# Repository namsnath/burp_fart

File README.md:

# burp_fart
A 3x5+3 split, diode-less keyboard with support for a rotary encoder.

## PCB

## Schematic

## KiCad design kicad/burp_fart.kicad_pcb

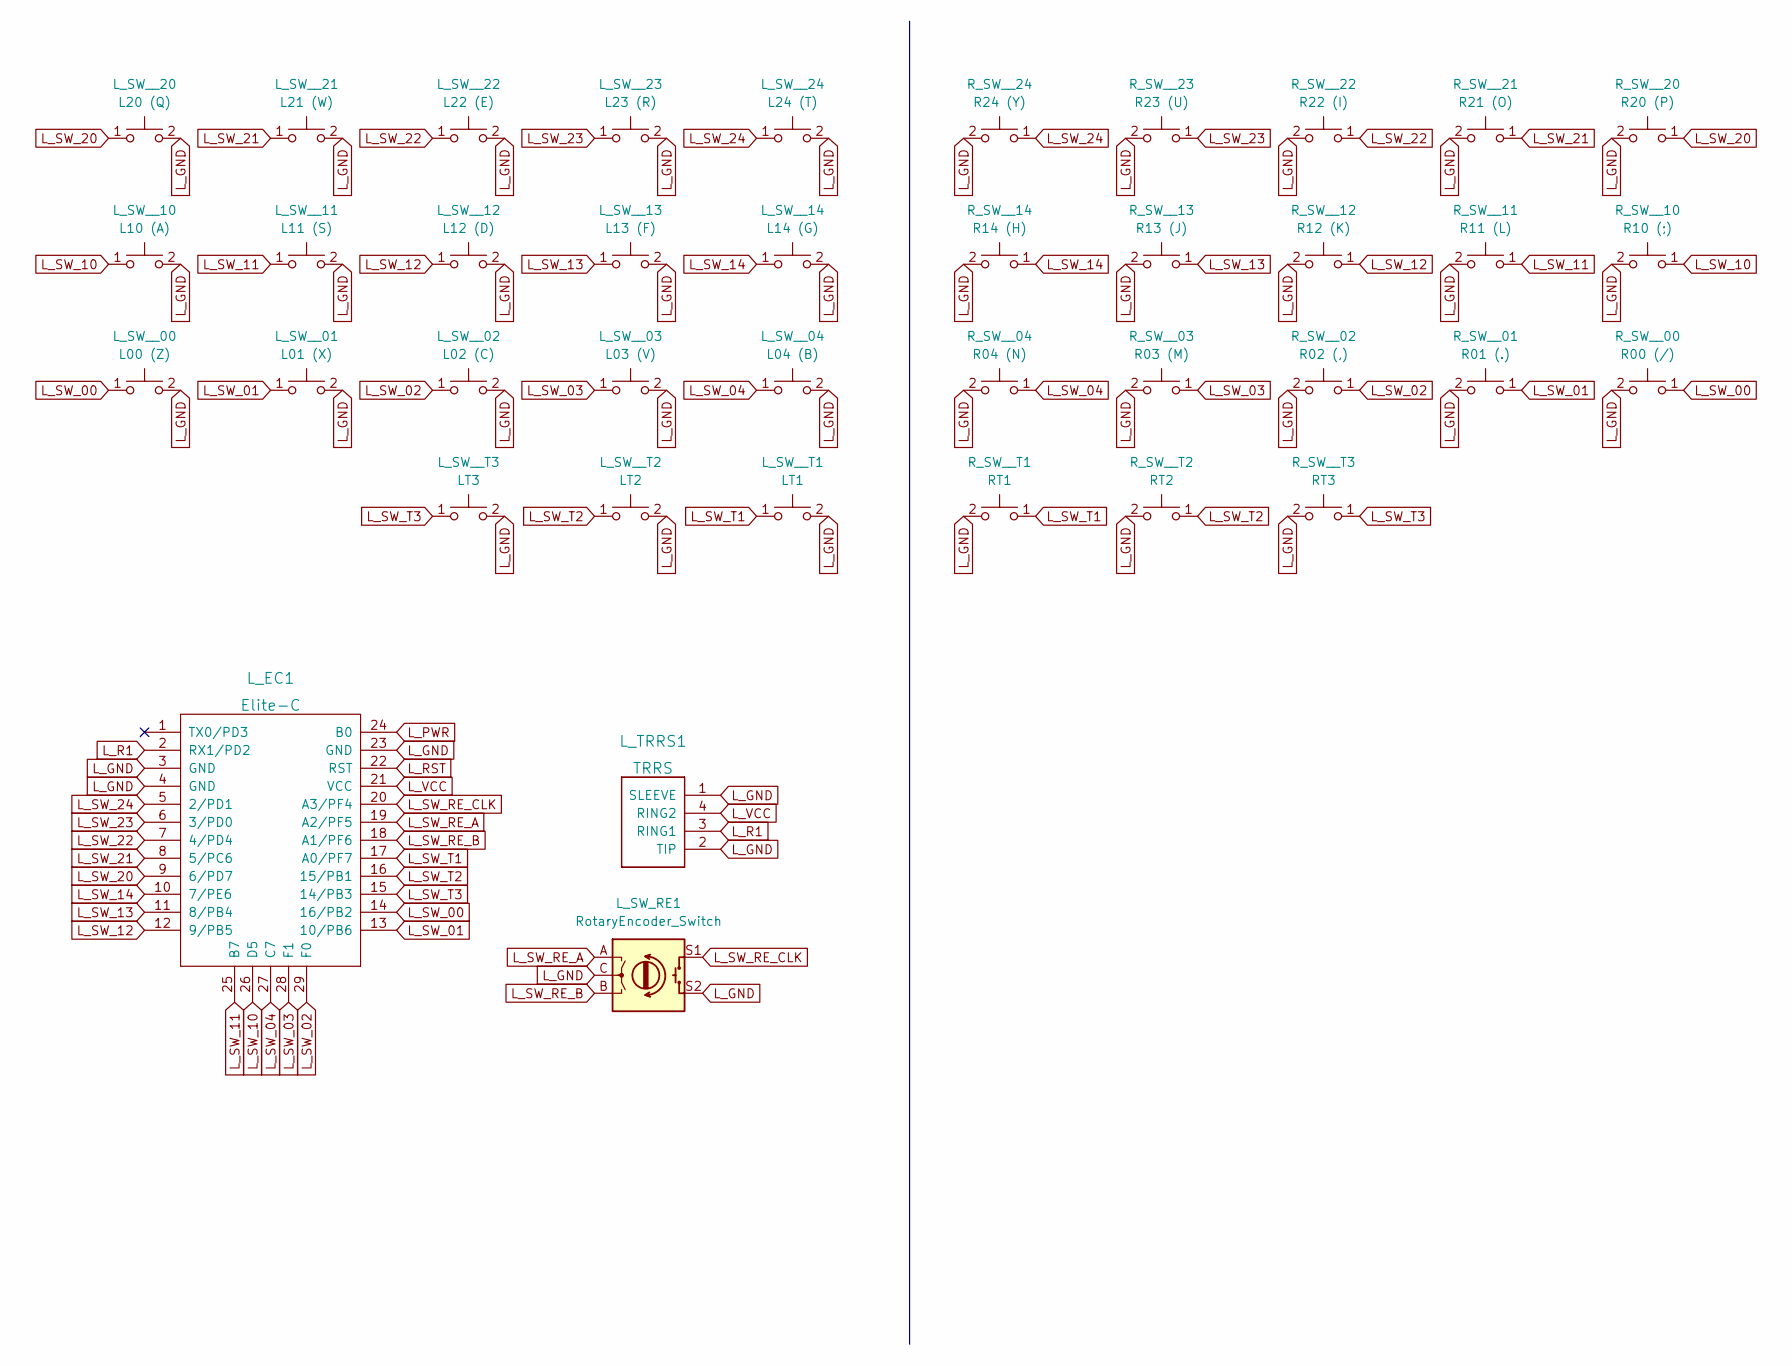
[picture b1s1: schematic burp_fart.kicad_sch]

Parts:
L_EC1: Elite-C
L_SW_RE1: RotaryEncoder_Switch; RotaryEncoder_Alps_EC11E-Switch_Vertical_H20mm
L_SW__00: L00 (Z); Kailh_socket_MX_pads_flipped
L_SW__01: L01 (X); Kailh_socket_MX_pads_flipped
L_SW__02: L02 (C); Kailh_socket_MX_pads_flipped
L_SW__03: L03 (V); Kailh_socket_MX_pads_flipped
L_SW__04: L04 (B); Kailh_socket_MX_pads_flipped
L_SW__10: L10 (A); Kailh_socket_MX_pads_flipped
L_SW__11: L11 (S); Kailh_socket_MX_pads_flipped
L_SW__12: L12 (D); Kailh_socket_MX_pads_flipped
L_SW__13: L13 (F); Kailh_socket_MX_pads_flipped
L_SW__14: L14 (G); Kailh_socket_MX_pads_flipped
L_SW__20: L20 (Q); Kailh_socket_MX_pads_flipped
L_SW__21: L21 (W); Kailh_socket_MX_pads_flipped
L_SW__22: L22 (E); Kailh_socket_MX_pads_flipped
L_SW__23: L23 (R); Kailh_socket_MX_pads_flipped
L_SW__24: L24 (T); Kailh_socket_MX_pads_flipped
L_SW__T1: LT1; Kailh_socket_MX_pads_flipped
L_SW__T2: LT2; Kailh_socket_MX_pads_flipped
L_SW__T3: LT3; Kailh_socket_MX_pads_flipped
L_TRRS1: TRRS; TRRS-PJ-320A_reversible
R_SW__00: R00 (/); Kailh_socket_MX_pads_flipped
R_SW__01: R01 (.); Kailh_socket_MX_pads_flipped
R_SW__02: R02 (,); Kailh_socket_MX_pads_flipped
R_SW__03: R03 (M); Kailh_socket_MX_pads_flipped
R_SW__04: R04 (N); Kailh_socket_MX_pads_flipped
R_SW__10: R10 (;); Kailh_socket_MX_pads_flipped
R_SW__11: R11 (L); Kailh_socket_MX_pads_flipped
R_SW__12: R12 (K); Kailh_socket_MX_pads_flipped
R_SW__13: R13 (J); Kailh_socket_MX_pads_flipped
R_SW__14: R14 (H); Kailh_socket_MX_pads_flipped
R_SW__20: R20 (P); Kailh_socket_MX_pads_flipped
R_SW__21: R21 (O); Kailh_socket_MX_pads_flipped
R_SW__22: R22 (I); Kailh_socket_MX_pads_flipped
R_SW__23: R23 (U); Kailh_socket_MX_pads_flipped
R_SW__24: R24 (Y); Kailh_socket_MX_pads_flipped
R_SW__T1: RT1; Kailh_socket_MX_pads_flipped
R_SW__T2: RT2; Kailh_socket_MX_pads_flipped
R_SW__T3: RT3; Kailh_socket_MX_pads_flipped

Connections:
L_GND: L_EC1.3 (GND), L_EC1.4 (GND), L_EC1.23 (GND), L_SW_RE1.C, L_SW_RE1.S2, L_SW__00.2, L_SW__01.2, L_SW__02.2, L_SW__03.2, L_SW__04.2, L_SW__10.2, L_SW__11.2, L_SW__12.2, L_SW__13.2, L_SW__14.2, L_SW__20.2, L_SW__21.2, L_SW__22.2, L_SW__23.2, L_SW__24.2, L_SW__T1.2, L_SW__T2.2, L_SW__T3.2, L_TRRS1.1 (SLEEVE), L_TRRS1.2 (TIP), R_SW__00.2, R_SW__01.2, R_SW__02.2, R_SW__03.2, R_SW__04.2, R_SW__10.2, R_SW__11.2, R_SW__12.2, R_SW__13.2, R_SW__14.2, R_SW__20.2, R_SW__21.2, R_SW__22.2, R_SW__23.2, R_SW__24.2, R_SW__T1.2, R_SW__T2.2, R_SW__T3.2
L_PWR: L_EC1.24 (B0)
L_R1: L_EC1.2 (RX1/PD2), L_TRRS1.3 (RING1)
L_RST: L_EC1.22 (RST)
L_SW_00: L_EC1.14 (16/PB2), L_SW__00.1, R_SW__00.1
L_SW_01: L_EC1.13 (10/PB6), L_SW__01.1, R_SW__01.1
L_SW_02: L_EC1.29 (F0), L_SW__02.1, R_SW__02.1
L_SW_03: L_EC1.28 (F1), L_SW__03.1, R_SW__03.1
L_SW_04: L_EC1.27 (C7), L_SW__04.1, R_SW__04.1
L_SW_10: L_EC1.26 (D5), L_SW__10.1, R_SW__10.1
L_SW_11: L_EC1.25 (B7), L_SW__11.1, R_SW__11.1
L_SW_12: L_EC1.12 (9/PB5), L_SW__12.1, R_SW__12.1
L_SW_13: L_EC1.11 (8/PB4), L_SW__13.1, R_SW__13.1
L_SW_14: L_EC1.10 (7/PE6), L_SW__14.1, R_SW__14.1
L_SW_20: L_EC1.9 (6/PD7), L_SW__20.1, R_SW__20.1
L_SW_21: L_EC1.8 (5/PC6), L_SW__21.1, R_SW__21.1
L_SW_22: L_EC1.7 (4/PD4), L_SW__22.1, R_SW__22.1
L_SW_23: L_EC1.6 (3/PD0), L_SW__23.1, R_SW__23.1
L_SW_24: L_EC1.5 (2/PD1), L_SW__24.1, R_SW__24.1
L_SW_RE_A: L_EC1.19 (A2/PF5), L_SW_RE1.A
L_SW_RE_B: L_EC1.18 (A1/PF6), L_SW_RE1.B
L_SW_RE_CLK: L_EC1.20 (A3/PF4), L_SW_RE1.S1
L_SW_T1: L_EC1.17 (A0/PF7), L_SW__T1.1, R_SW__T1.1
L_SW_T2: L_EC1.16 (15/PB1), L_SW__T2.1, R_SW__T2.1
L_SW_T3: L_EC1.15 (14/PB3), L_SW__T3.1, R_SW__T3.1
L_VCC: L_EC1.21 (VCC), L_TRRS1.4 (RING2)

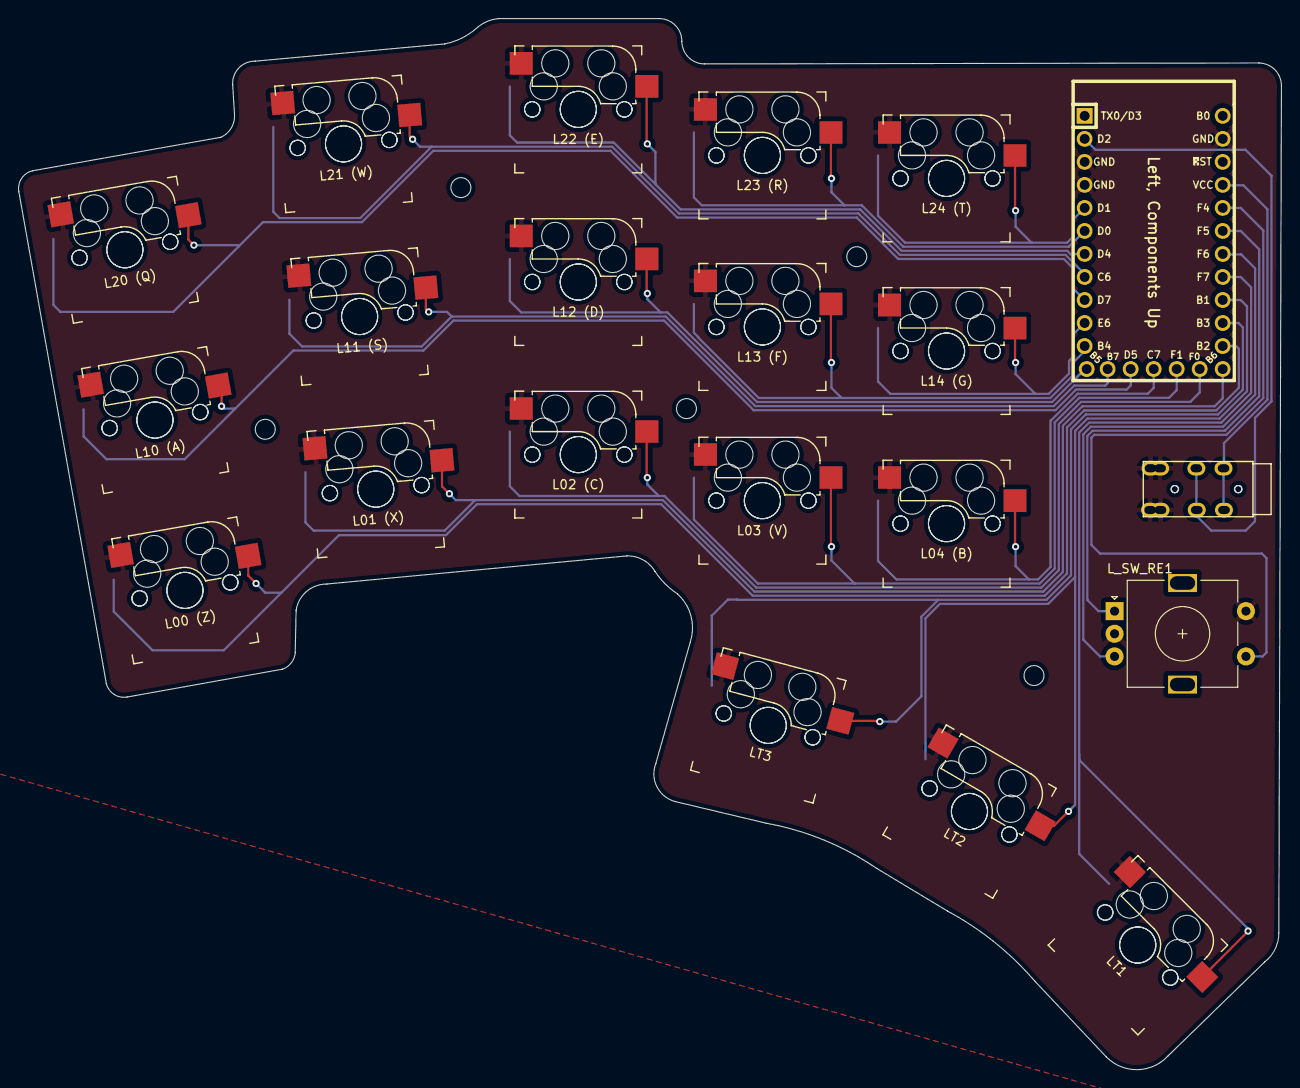
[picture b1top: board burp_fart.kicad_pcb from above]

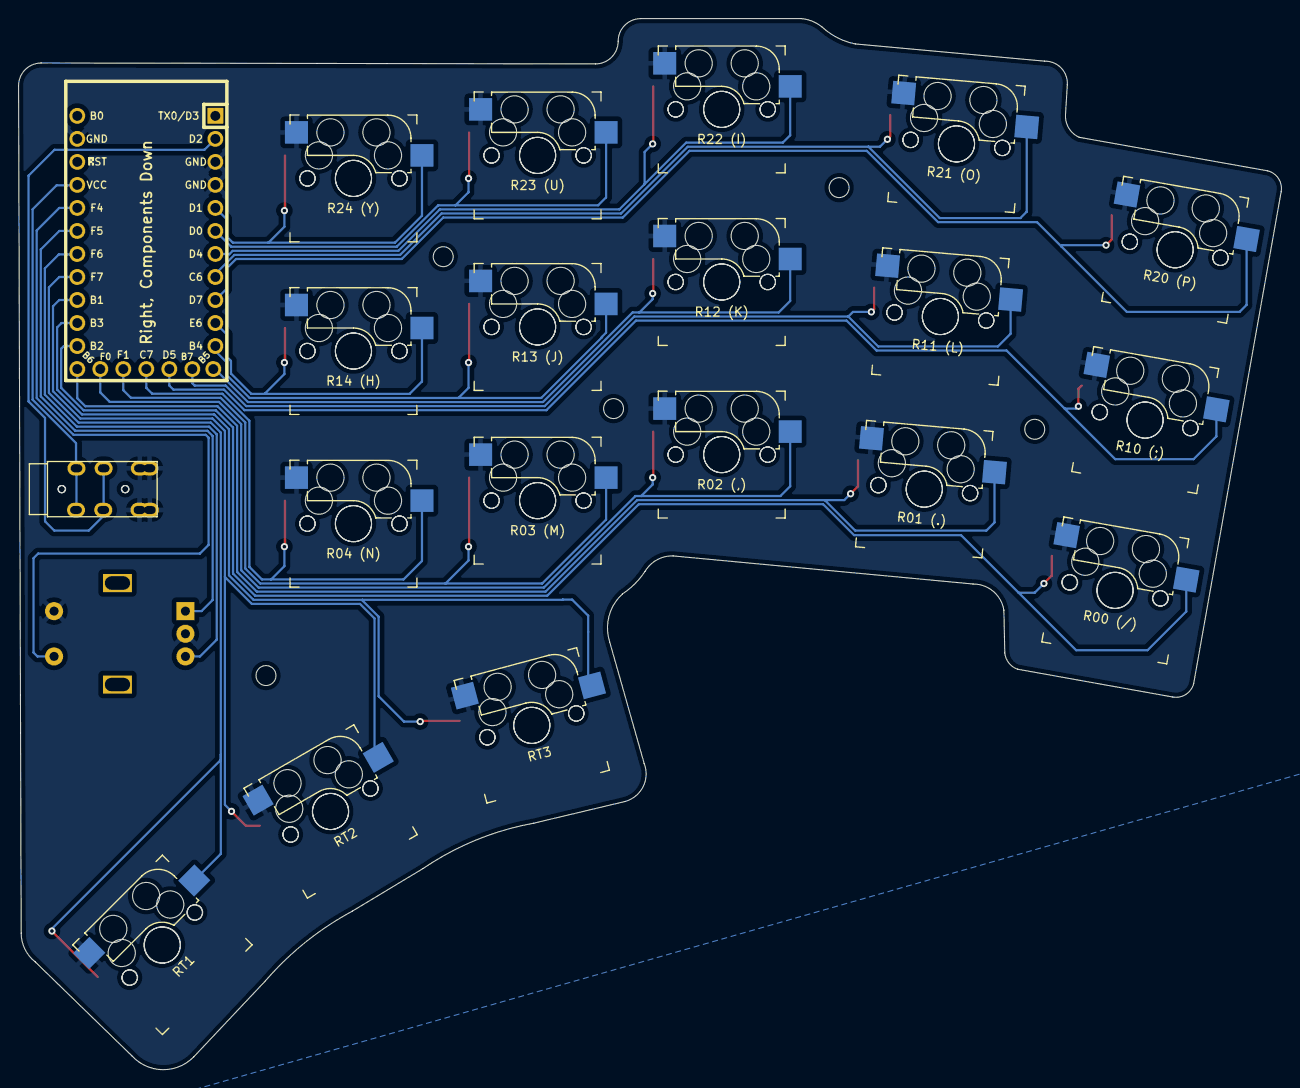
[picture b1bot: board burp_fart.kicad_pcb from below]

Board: 2 copper layers, 139.4 x 116.0 mm, 39 parts (18 on the bottom side), 24 nets.

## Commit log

2022-09-02 feat: adds PCB design and libs
2022-09-03 feat: adds readme and images
2022-09-04 update: makes edges rounded
2022-09-04 feat: adds gerbers
2022-09-04 update: gerbers
